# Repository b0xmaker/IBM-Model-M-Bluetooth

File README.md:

# IBM-Model-M-Bluetooth

An Adafruit ItsyBitsy based mod for the IBM model M keyboard to give bluetooth capability

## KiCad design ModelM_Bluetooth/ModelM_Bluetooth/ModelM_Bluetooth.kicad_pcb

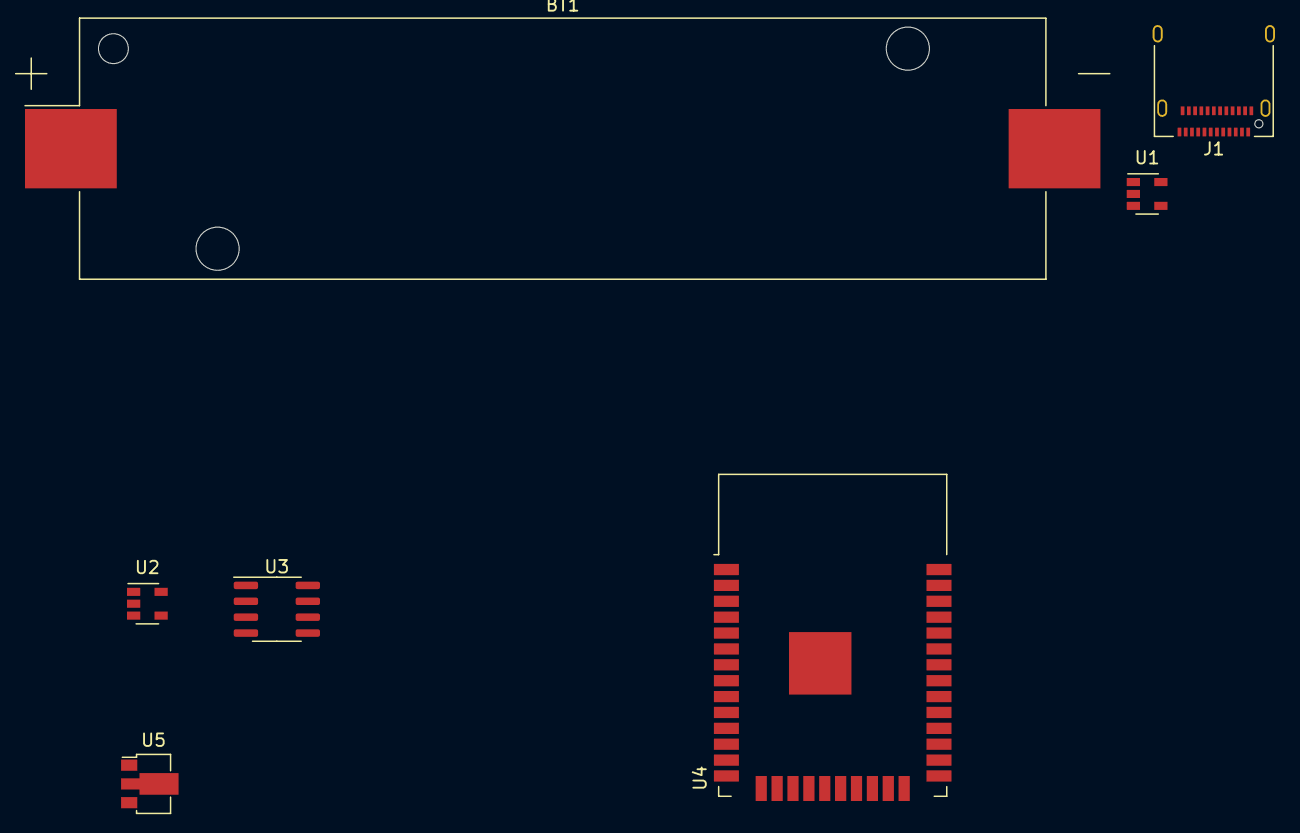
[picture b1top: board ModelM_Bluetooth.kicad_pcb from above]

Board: 2 copper layers, 7 parts (0 on the bottom side), 4 nets, no tracks yet.

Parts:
BT1: Battery_Cell; BatteryHolder_Keystone_1042_1x18650
J1: USB_C_Receptacle_USB2.0; USB_C_Receptacle_Amphenol_12401610E4-2A
U1: MCP73831-2-OT; SOT-23-5
U2: AP2112K-3.3; SOT-23-5
U3: L78L05_SO8; SOIC-8_3.9x4.9mm_P1.27mm
U4: ESP32-WROOM-32
U5: L78L05_SOT89; SOT-89-3

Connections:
unnamed: J1.A1, J1.A12, J1.B1, J1.B12
unnamed: J1.A4, J1.A9, J1.B4, J1.B9
unnamed: U3.2, U3.3, U3.6, U3.7
unnamed: U4.1, U4.15, U4.38, U4.39

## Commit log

2021-03-07 via Ben Eater
    https://docs.google.com/document/d/1w--ouGvSSf93tFltmBcSRGMN8Rte7ayalQZRDPG0ezk/edit
2021-03-07 Create pinout
